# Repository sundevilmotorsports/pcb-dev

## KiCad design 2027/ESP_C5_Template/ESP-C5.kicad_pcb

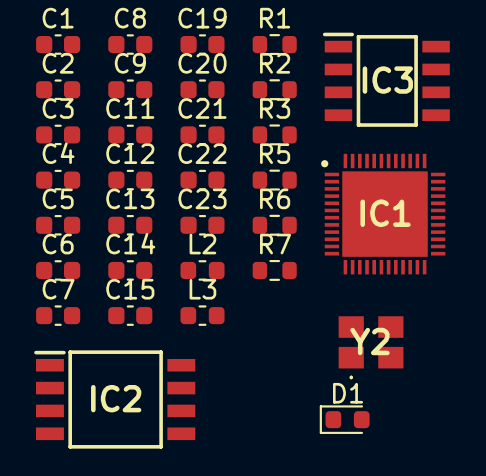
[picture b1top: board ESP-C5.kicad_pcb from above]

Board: 2 copper layers, 32 parts (0 on the bottom side), 20 nets, no tracks yet.

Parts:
C1: 0.8pF; C_0603_1608Metric
C2, C3: 12pF; C_0603_1608Metric
C4: 0.3pF; C_0603_1608Metric
C5, C19, C23: 10uF; C_0603_1608Metric
C6, C8, C14: 1uF; C_0603_1608Metric
C7, C11, C13, C20, C22: 0.1uF; C_0603_1608Metric
C9: 2.6pF; C_0603_1608Metric
C12: 10nF; C_0603_1608Metric
C15: 1 uF; C_0603_1608Metric
C21: 3.0pF; C_0603_1608Metric
D1: D_TVS (ESD); D_0603_1608Metric
IC1: ESP32-C5HR8; QFN40P600X600X90-49N-D
IC2: SST26VF064B-104I_SM; SOIC127P794X203-8N
IC3: IS66WVR8M8FBLL-104NLI; SOIC127P600X175-8N
L2: 24nH; L_0603_1608Metric
L3: 2nH; L_0603_1608Metric
R1: 499; R_0603_1608Metric
R2, R3, R5, R6, R7: 0; R_0603_1608Metric
Y2: CX3225FB48000F0FZZH1

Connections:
/SPICLK: IC2.6 (CLK), IC3.6 (CLK), R6.2
/SPICS0: IC1.26 (SPICS0), IC2.1 (~CS)
/SPICS1_IO15: IC1.25 (SPICS1), IC3.1 (~CS)
/SPID: IC2.5 (DI), IC3.5 (DI), R7.2
/SPIHD: IC2.7 (~HOLD), IC3.7 (~HOLD), R5.2
/SPIQ: IC2.2 (DO), IC3.2 (DO), R2.2
/SPIWP: IC2.3 (~WP), IC3.3 (~WP), R3.2
/VDD33: C1.1, C4.1, C5.1, C6.1, C7.1, C8.1, C11.1, C12.1, C13.1, C14.1, C19.1, C21.1, C22.1, C23.1, D1.1 (A1), IC1.1 (VDDA6), IC1.3 (VDDA7), IC1.6 (VDDA8), IC1.8 (VDDPST1), IC1.24 (VDDPST2), IC1.39 (VDDPST3), IC1.44 (VDDA3), IC1.45 (VDDA4), IC1.46 (VDDA5), L3.2
/VDD_SPI: C15.1, C20.1, IC1.29 (VDD_SPI), IC2.8 (VDD), IC3.8 (VDD)
/XTAL_N: C2.2, IC1.4 (XTAL_N), Y2.3 (X_OUT)
/XTAL_P: C3.2, L2.1, Y2.1 (X_IN)
GND: C1.2, C2.1, C3.1, C4.2, C5.2, C6.2, C7.2, C8.2, C9.2, C11.2, C12.2, C13.2, C14.2, C15.2, C19.2, C20.2, C21.2, C22.2, C23.2, D1.2 (A2), IC1.2 (GND_1), IC1.43 (GND_2), IC1.47 (GND_3), IC1.49 (GND_4), IC2.4 (GND), IC3.4 (GND), Y2.2 (GND_1), Y2.4 (GND_2)
unnamed: IC1.31 (SPICLK), R6.1
unnamed: IC1.32 (SPID), R7.1
unnamed: IC1.30 (SPIHD), R5.1
unnamed: IC1.27 (SPIQ), R2.1
unnamed: IC1.28 (SPIWP), R3.1
unnamed: IC1.20 (U0TXD), R1.1
unnamed: C9.1, IC1.40 (VDDA1), IC1.41 (VDDA2), L3.1
unnamed: IC1.5 (XTAL_P), L2.2

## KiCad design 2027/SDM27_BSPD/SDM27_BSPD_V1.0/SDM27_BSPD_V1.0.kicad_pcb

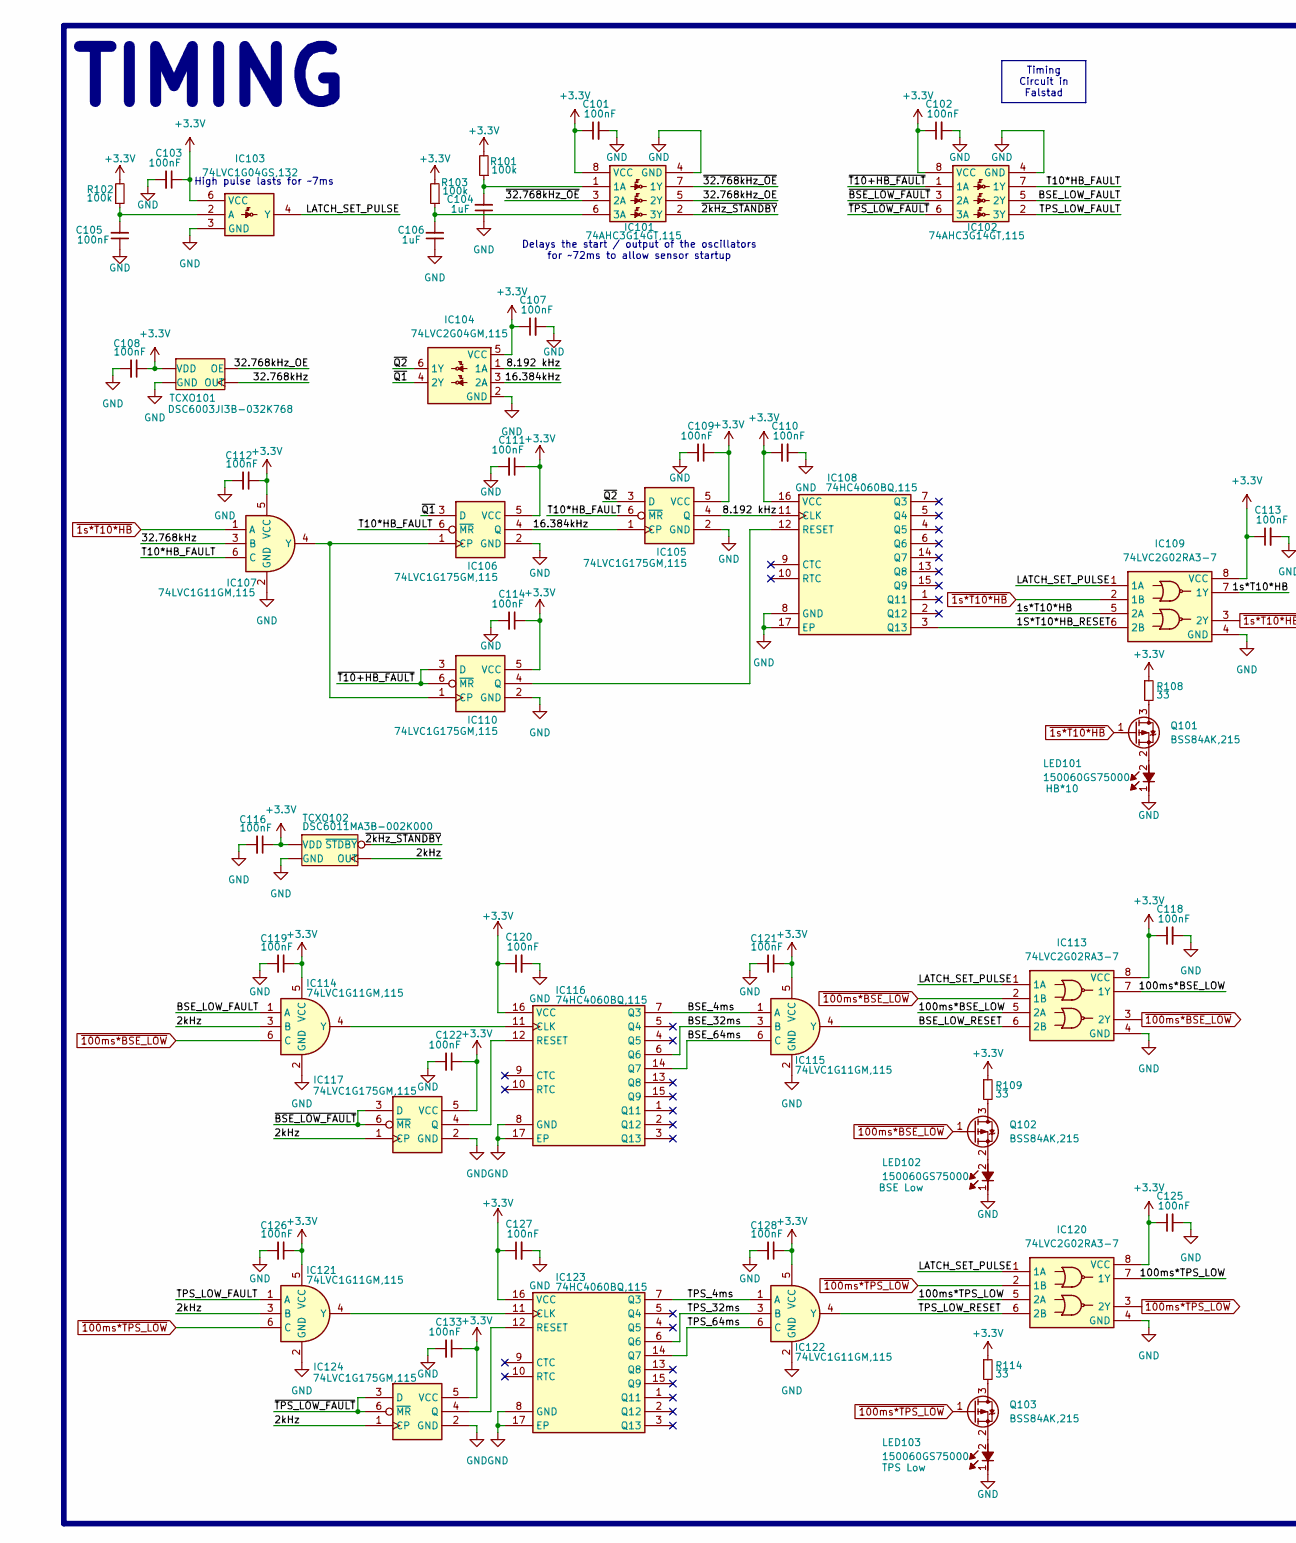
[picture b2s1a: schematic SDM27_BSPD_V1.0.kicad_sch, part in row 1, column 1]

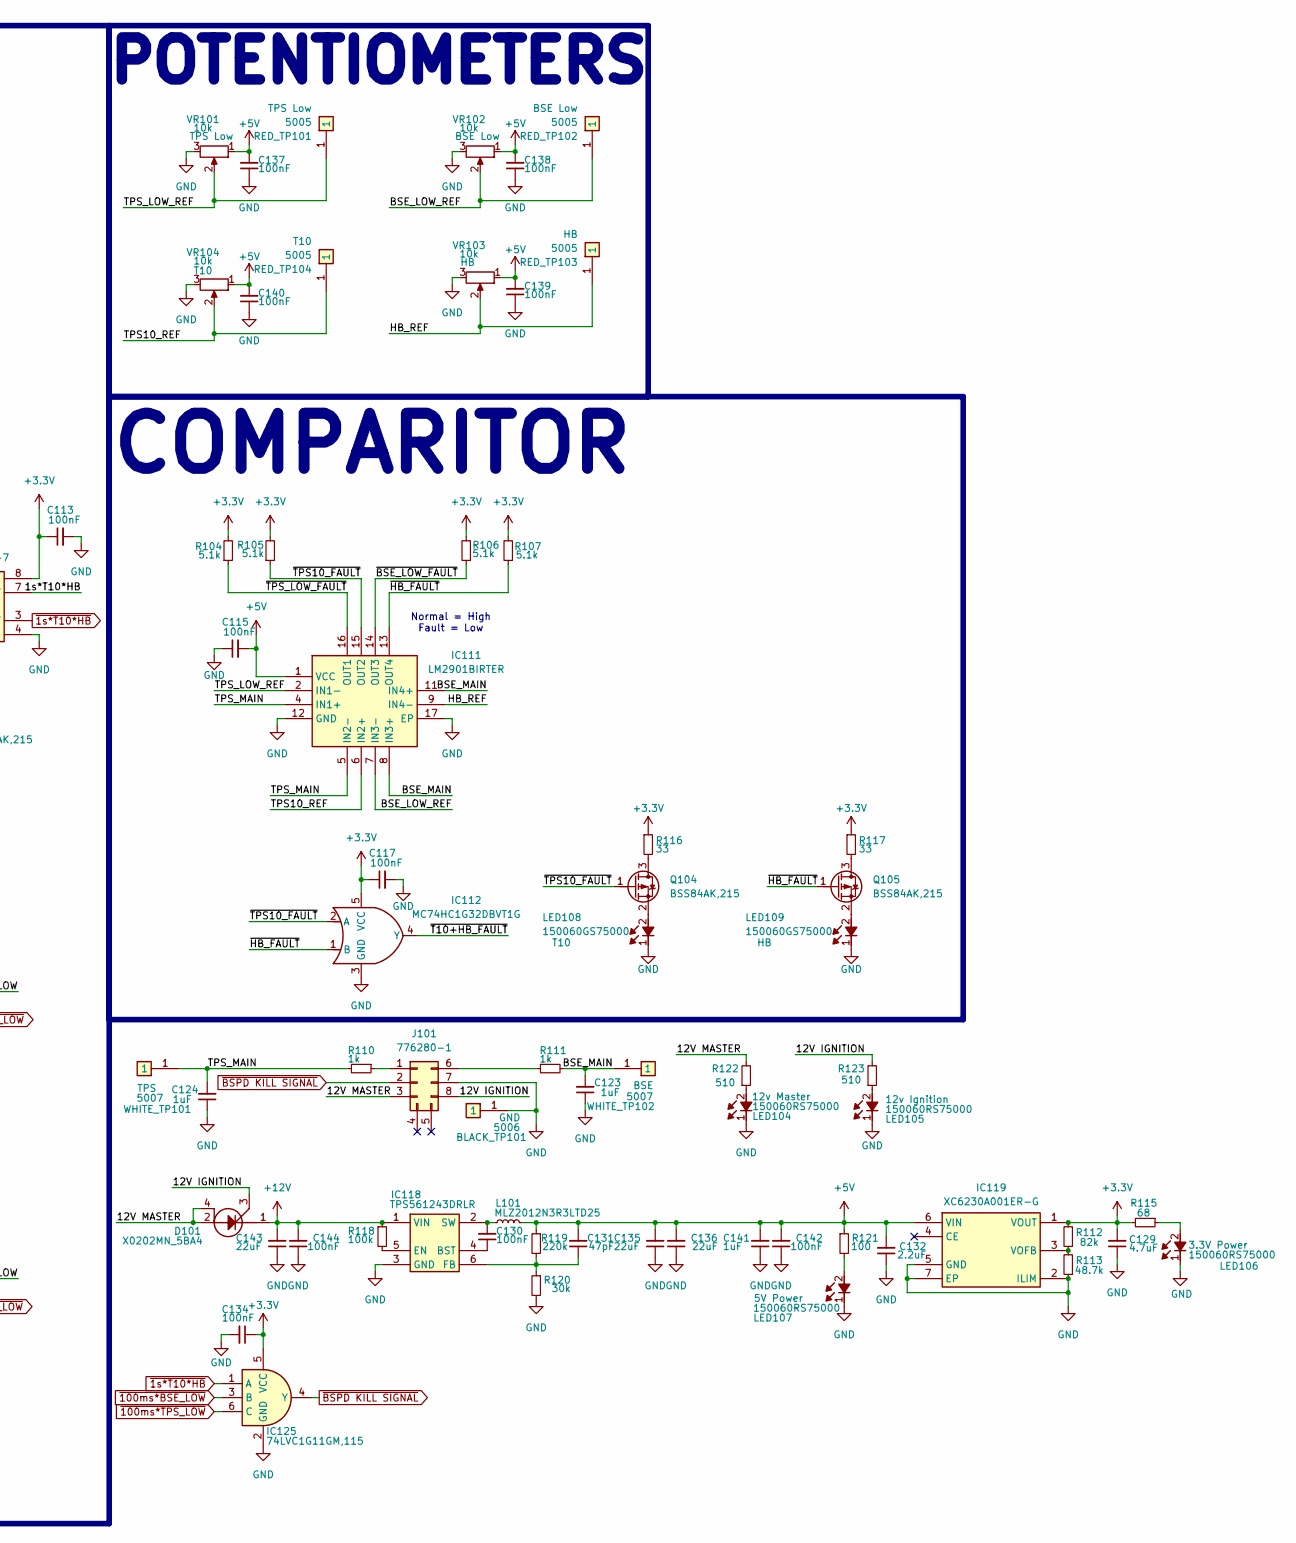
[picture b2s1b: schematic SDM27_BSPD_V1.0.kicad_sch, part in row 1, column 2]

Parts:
BLACK_TP101: 5006; Mouser Part Number 534-5006
C101, C102, C103, C105, C107, C108, C109, C110, C111, C112, C113, C114, C115, C116, C117, C118, C119, C120, C121, C122, C125, C126, C127, C128, C130, C133, C134, C137, C138, C139, C140, C142, C144: 100nF; C_0603_1608Metric
C104, C106, C123, C124, C141: 1uF; C_0603_1608Metric
C129: 4.7uF; C_0603_1608Metric
C131: 47pF; C_0603_1608Metric
C132: 2.2uF; C_0603_1608Metric
C135, C136: 22uF; C_0805_2012Metric
C143: 22uF; C_0603_1608Metric
D101: X0202MN_5BA4; SOT230P700X190-4N; Mouser Part Number 511-X0202MN
IC101, IC102: 74AHC3G14GT,115; 74AVC9112GTX; Mouser Part Number 771-74AHC3G14GT115
IC103: 74LVC1G04GS,132; 74LVC1G3157GS132; Mouser Part Number 771-74LVC1G04GS132
IC104: 74LVC2G04GM,115; PESD3V3L5UF115; Mouser Part Number 771-LVC2G04GM115
IC105, IC106, IC110, IC117, IC124: 74LVC1G175GM,115; PESD3V3L5UF115; Mouser Part Number 771-LVC1G175GM115
IC107, IC114, IC115, IC121, IC122, IC125: 74LVC1G11GM,115; PESD3V3L5UF115; Mouser Part Number 771-LVC1G11GM115
IC108, IC116, IC123: 74HC4060BQ,115; 74HC4060BQ115; Mouser Part Number 771-74HC4060BQ,115
IC109, IC113, IC120: 74LVC2G02RA3-7; 74LVC2G02RA37; Mouser Part Number 621-74LVC2G02RA3-7
IC111: LM2901BIRTER; QFN50P300X300X80-17N-D; Mouser Part Number 595-LM2901BIRTER
IC112: MC74HC1G32DBVT1G; SOT95P275X110-5L; Mouser Part Number 863-MC74HC1G32DBVT1G
IC118: TPS561243DRLR; SOTFL50P160X60-6L; Mouser Part Number 595-TPS561243DRLR
IC119: XC6230A001ER-G; XD9264D75DERQ; Manufacturer_Part_Number XC6230A001ER-G
J101: 776280-1; Mouser Part Number 571-776280-1
L101: MLZ2012N3R3LTD25; INDC2012X105L; Mouser Part Number 810-MLZ2012N3R3LTD25
LED101, LED102, LED103, LED108, LED109: 150060GS75000; LEDC1608X80N; Mouser Part Number 710-150060GS75000
LED104, LED105, LED106, LED107: 150060RS75000; LEDC1608X80N; Mouser Part Number 710-150060RS75000
Q101, Q102, Q103, Q104, Q105: BSS84AK,215; SOT95P230X110-3L; Mouser Part Number 771-BSS84AK215
R101, R102, R103, R118: 100k; R_0603_1608Metric
R104, R105, R106, R107: 5.1k; R_0603_1608Metric
R108, R109, R114, R116, R117: 33; R_0603_1608Metric
R110, R111: 1k; R_0603_1608Metric
R112: 82k; R_0603_1608Metric
R113: 48.7k; R_0603_1608Metric
R115: 68; R_0603_1608Metric
R119: 220k; R_0603_1608Metric
R120: 30k; R_0603_1608Metric
R121: 100; R_0603_1608Metric
R122, R123: 510; R_0603_1608Metric
RED_TP101, RED_TP102, RED_TP103, RED_TP104: 5005; Mouser Part Number 534-5005
TCXO101: DSC6003JI3B-032K768; Mouser Part Number 579-D6003JI3B032K768
TCXO102: DSC6011MA3B-002K000; Mouser Part Number 579-C6011MA3B02K000
VR101, VR102, VR103, VR104: 10k; 3386P1103TLF; Mouser Part Number 652-3386P-1-103TLF
WHITE_TP101, WHITE_TP102: 5007; Mouser Part Number 534-5007

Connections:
+3.3V: C101.1, C102.1, C103.1, C107.1, C108.1, C109.1, C110.1, C111.1, C112.1, C113.1, C114.1, C116.1, C117.1, C118.1, C119.1, C120.1, C121.1, C122.1, C125.1, C126.1, C127.1, C128.1, C129.2, C133.1, C134.1, IC101.8 (VCC), IC102.8 (VCC), IC103.6 (VCC), IC104.5 (VCC), IC105.5 (VCC), IC106.5 (VCC), IC107.5 (VCC), IC108.16 (VCC), IC109.8 (VCC), IC110.5 (VCC), IC112.5 (VCC), IC113.8 (VCC), IC114.5 (VCC), IC115.5 (VCC), IC116.16 (VCC), IC117.5 (VCC), IC119.1 (VOUT), IC120.8 (VCC), IC121.5 (VCC), IC122.5 (VCC), IC123.16 (VCC), IC124.5 (VCC), IC125.5 (VCC), R101.2, R102.2, R103.2, R104.2, R105.2, R106.2, R107.2, R108.1, R109.1, R112.2, R114.1, R115.2, R116.1, R117.1, TCXO101.4 (VDD), TCXO102.4 (VDD)
+5V: C115.2, C131.2, C132.2, C135.2, C136.2, C137.2, C138.2, C139.2, C140.2, C141.2, C142.2, IC111.1 (VCC), IC119.6 (VIN), L101.2, R119.1, R121.1, VR101.1 (CCW), VR102.1 (CCW), VR103.1 (CCW), VR104.1 (CCW)
+12V: C143.2, C144.2, D101.1 (K), IC118.1 (VIN), R118.1
/1S*T10*HB_RESET: IC108.3 (Q13), IC109.6 (2B)
/1s*T10*HB: IC109.5 (2A), IC109.7 (1Y)
/2kHz: IC114.3 (B), IC117.1 (CP), IC121.3 (B), IC124.1 (CP), TCXO102.3 (OUT)
/8.192 kHz: IC104.1 (1A), IC105.4 (Q), IC108.11 (CLK)
/12V IGNITION: D101.3 (G), J101.8, R123.2
/12V MASTER: D101.2 (A_1), D101.4 (A_2), J101.3, R122.2
/16.384kHz: IC104.3 (2A), IC105.1 (CP), IC106.4 (Q)
/32.768kHz: IC107.3 (B), TCXO101.3 (OUT)
/32.768kHz_OE: IC101.5 (2Y), TCXO101.1 (OE)
/100ms*BSE_LOW: IC113.5 (2A), IC113.7 (1Y)
/100ms*TPS_LOW: IC120.5 (2A), IC120.7 (1Y)
/BSE_4ms: IC115.1 (A), IC116.7 (Q3)
/BSE_32ms: IC115.3 (B), IC116.6 (Q6)
/BSE_64ms: IC115.6 (C), IC116.14 (Q7)
/BSE_LOW_FAULT: IC102.5 (2Y), IC114.1 (A)
/BSE_LOW_REF: IC111.7 (IN3-), RED_TP102.1, VR102.2 (Wiper)
/BSE_LOW_RESET: IC113.6 (2B), IC115.4 (Y)
/BSE_MAIN: C123.2, IC111.8 (IN3+), IC111.11 (IN4+), R111.2, WHITE_TP102.1
/HB_REF: IC111.9 (IN4-), RED_TP103.1, VR103.2 (Wiper)
/LATCH_SET_PULSE: IC103.4 (Y), IC109.1 (1A), IC113.1 (1A), IC120.1 (1A)
/T10*HB_FAULT: IC102.7 (1Y), IC105.6 (~MR), IC106.6 (~MR), IC107.6 (C)
/TPS10_REF: IC111.6 (IN2+), RED_TP104.1, VR104.2 (Wiper)
/TPS_4ms: IC122.1 (A), IC123.7 (Q3)
/TPS_32ms: IC122.3 (B), IC123.6 (Q6)
/TPS_64ms: IC122.6 (C), IC123.14 (Q7)
/TPS_LOW_FAULT: IC102.2 (3Y), IC121.1 (A)
/TPS_LOW_REF: IC111.2 (IN1-), RED_TP101.1, VR101.2 (Wiper)
/TPS_LOW_RESET: IC120.6 (2B), IC122.4 (Y)
/TPS_MAIN: C124.2, IC111.4 (IN1+), IC111.5 (IN2-), R110.2, WHITE_TP101.1
/~2kHz_STANDBY: IC101.2 (3Y), TCXO102.1 (~STDBY)
/~32.768kHz_OE: IC101.3 (2A), IC101.7 (1Y)
/~BSE_LOW_FAULT: IC102.3 (2A), IC111.14 (OUT3), IC117.3 (D), IC117.6 (~MR), R106.1
/~HB_FAULT: IC111.13 (OUT4), IC112.1 (B), Q105.1 (G), R107.1
/~Q1: IC104.4 (2Y), IC106.3 (D)
/~Q2: IC104.6 (1Y), IC105.3 (D)
/~T10+HB_FAULT: IC102.1 (1A), IC110.3 (D), IC110.6 (~MR), IC112.4 (Y)
/~TPS10_FAULT: IC111.15 (OUT2), IC112.2 (A), Q104.1 (G), R105.1
/~TPS_LOW_FAULT: IC102.6 (3A), IC111.16 (OUT1), IC124.3 (D), IC124.6 (~MR), R104.1
GND: BLACK_TP101.1, C101.2, C102.2, C103.2, C104.1, C105.1, C106.1, C107.2, C108.2, C109.2, C110.2, C111.2, C112.2, C113.2, C114.2, C115.1, C116.2, C117.2, C118.2, C119.2, C120.2, C121.2, C122.2, C123.1, C124.1, C125.2, C126.2, C127.2, C128.2, C129.1, C132.1, C133.2, C134.2, C135.1, C136.1, C137.1, C138.1, C139.1, C140.1, C141.1, C142.1, C143.1, C144.1, IC101.4 (GND), IC102.4 (GND), IC103.3 (GND), IC104.2 (GND), IC105.2 (GND), IC106.2 (GND), IC107.2 (GND), IC108.8 (GND), IC108.17 (EP), IC109.4 (GND), IC110.2 (GND), IC111.12 (GND), IC111.17 (EP), IC112.3 (GND), IC113.4 (GND), IC114.2 (GND), IC115.2 (GND), IC116.8 (GND), IC116.17 (EP), IC117.2 (GND), IC118.3 (GND), IC119.2 (ILIM), IC119.5 (GND), IC119.7 (EP), IC120.4 (GND), IC121.2 (GND), IC122.2 (GND), IC123.8 (GND), IC123.17 (EP), IC124.2 (GND), IC125.2 (GND), J101.7, LED101.1 (K), LED102.1 (K), LED103.1 (K), LED104.1 (K), LED105.1 (K), LED106.1 (K), LED107.1 (K), LED108.1 (K), LED109.1 (K), R113.1, R120.2, TCXO101.2 (GND), TCXO102.2 (GND), VR101.3 (CW), VR102.3 (CW), VR103.3 (CW), VR104.3 (CW)
unnamed: C104.2, IC101.1 (1A), R101.1
unnamed: C106.2, IC101.6 (3A), R103.1
unnamed: C105.2, IC103.2 (A), R102.1
unnamed: IC106.1 (CP), IC107.4 (Y), IC110.1 (CP)
unnamed: IC108.12 (RESET), IC110.4 (Q)
unnamed: IC114.4 (Y), IC116.11 (CLK)
unnamed: IC116.12 (RESET), IC117.4 (Q)
unnamed: C130.1, IC118.4 (BST)
unnamed: IC118.5 (EN), R118.2
unnamed: C131.1, IC118.6 (FB), R119.2, R120.1
unnamed: C130.2, IC118.2 (SW), L101.1
unnamed: IC119.3 (VOFB), R112.1, R113.2
unnamed: IC121.4 (Y), IC123.11 (CLK)
unnamed: IC123.12 (RESET), IC124.4 (Q)
unnamed: J101.1, R110.1
unnamed: J101.6, R111.1
unnamed: LED101.2 (A), Q101.2 (S)
unnamed: LED102.2 (A), Q102.2 (S)
unnamed: LED103.2 (A), Q103.2 (S)
unnamed: LED104.2 (A), R122.1
unnamed: LED105.2 (A), R123.1
unnamed: LED106.2 (A), R115.1
unnamed: LED107.2 (A), R121.2
unnamed: LED108.2 (A), Q104.2 (S)
unnamed: LED109.2 (A), Q105.2 (S)
unnamed: Q101.3 (D), R108.2
unnamed: Q102.3 (D), R109.2
unnamed: Q103.3 (D), R114.2
unnamed: Q104.3 (D), R116.2
unnamed: Q105.3 (D), R117.2
~1s*T10*HB: IC107.1 (A), IC109.2 (1B), IC109.3 (2Y), IC125.1 (A), Q101.1 (G)
~100ms*BSE_LOW: IC113.2 (1B), IC113.3 (2Y), IC114.6 (C), IC125.3 (B), Q102.1 (G)
~100ms*TPS_LOW: IC120.2 (1B), IC120.3 (2Y), IC121.6 (C), IC125.6 (C), Q103.1 (G)
~BSPD KILL SIGNAL: IC125.4 (Y), J101.2

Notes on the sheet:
POTENTIOMETERS
High pulse lasts for ~7ms
Delays the start / output of the oscillators for ~72ms to allow sensor startup
COMPARITOR
TIMING
Normal = High Fault = Low
Timing Circuit in Falstad

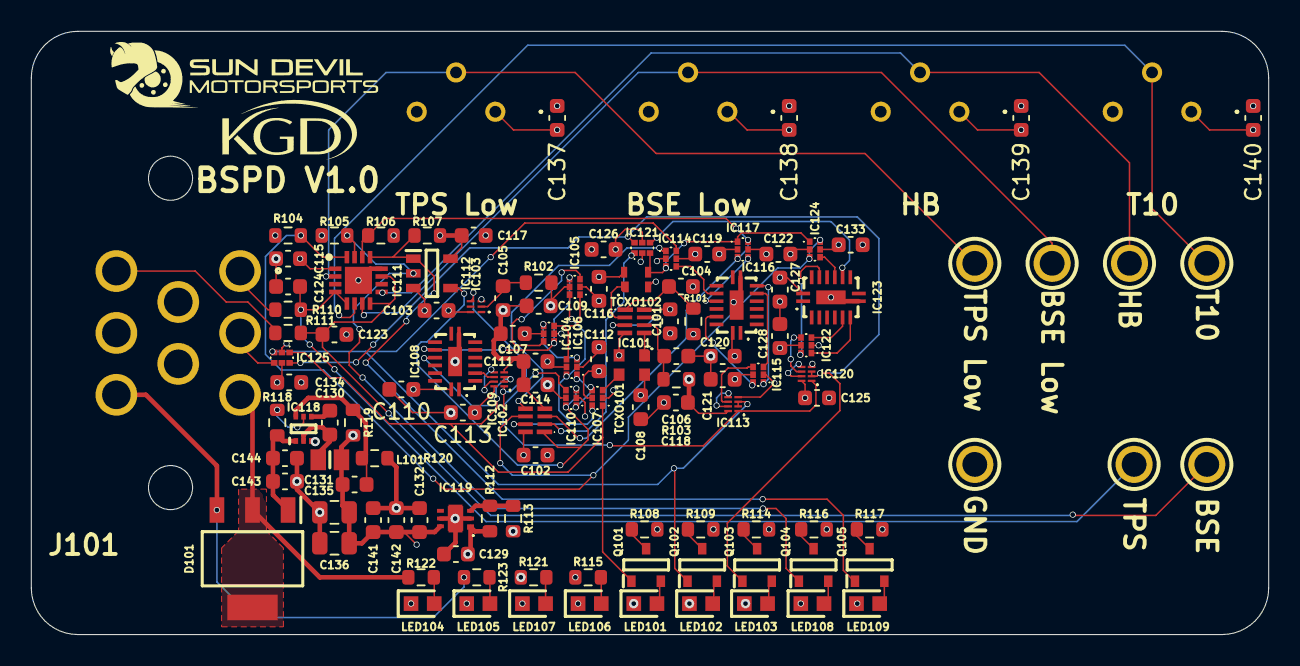
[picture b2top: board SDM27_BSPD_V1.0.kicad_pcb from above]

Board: 4 copper layers, 80.0 x 39.0 mm, 122 parts (0 on the bottom side), 76 nets.

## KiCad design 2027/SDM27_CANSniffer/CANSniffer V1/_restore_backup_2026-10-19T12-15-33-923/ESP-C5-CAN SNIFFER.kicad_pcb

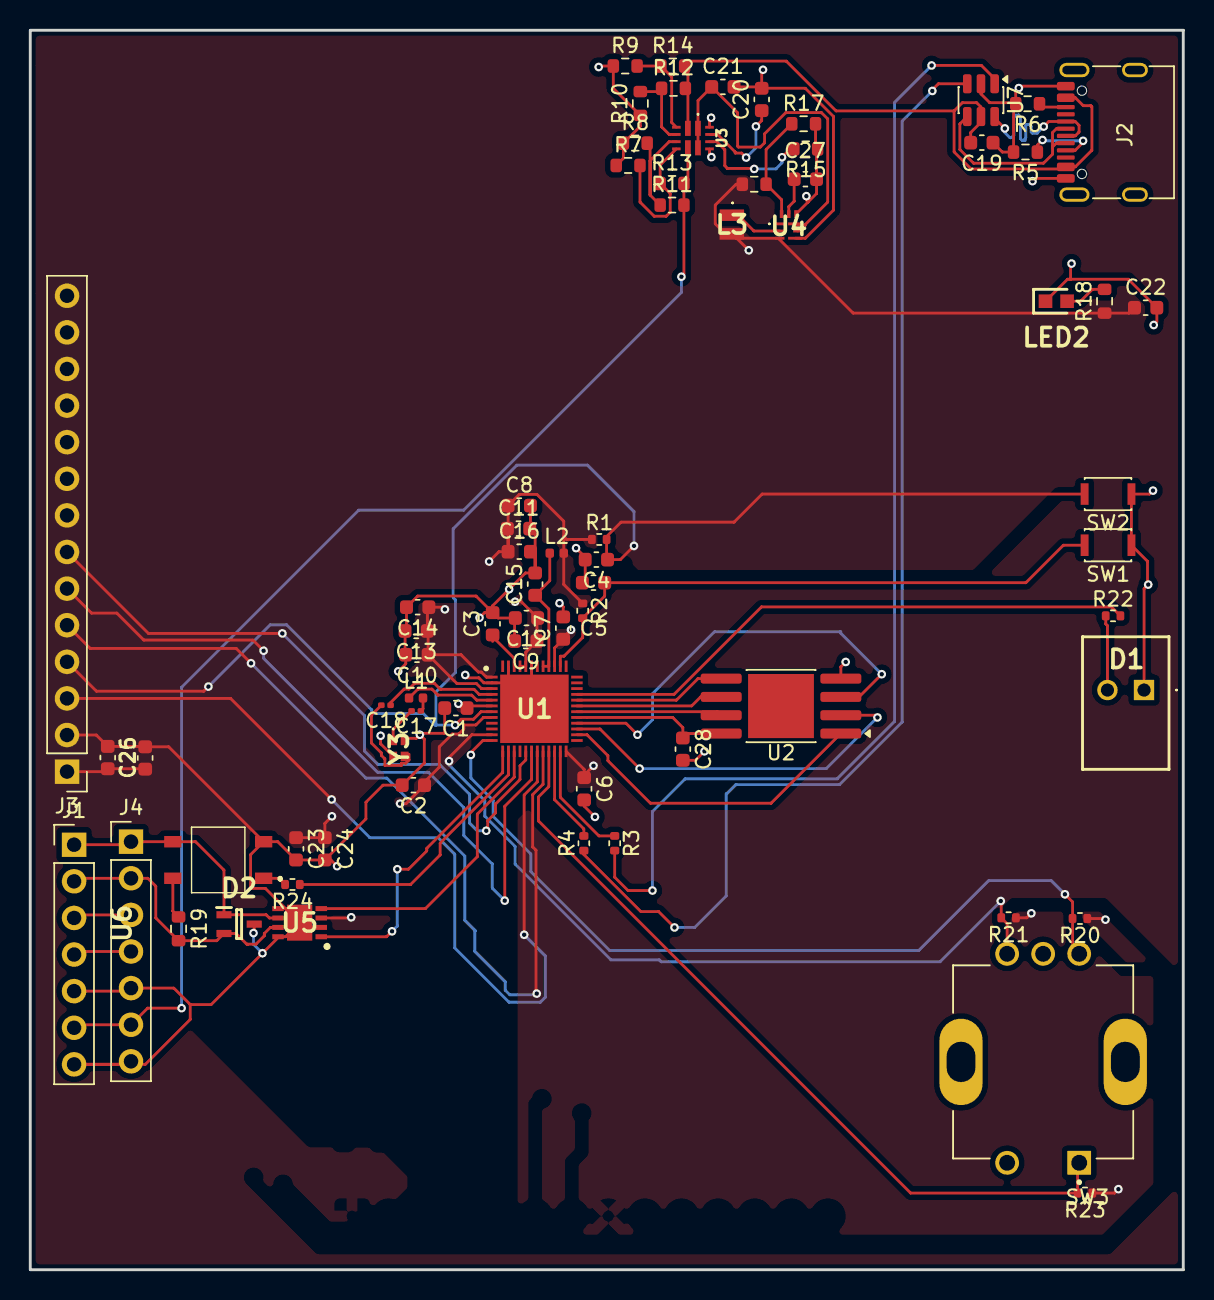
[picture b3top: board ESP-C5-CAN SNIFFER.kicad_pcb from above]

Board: 4 copper layers, 80.0 x 86.0 mm, 73 parts (0 on the bottom side), 57 nets.

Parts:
C1, C2, C3, C4, C5: 1uF; C_0603_1608Metric
C6, C7, C8, C9, C19, C23, C24, C25, C28: 100nF; C_0603_1608Metric
C10, C11, C12, C26: 10uF; C_0603_1608Metric
C13: 0.3pF; C_0603_1608Metric
C14: 0.8pF; C_0603_1608Metric
C15: 2.6pF; C_0603_1608Metric
C16: 3pF; C_0603_1608Metric
C17, C18: 12pF; C_0201_0603Metric
C20: 1uF 10V 0603; C_0603_1608Metric
C21: 10uF 25V; C_0603_1608Metric
C22: 22uF; C_0603_1608Metric
C27: 10nF; C_0603_1608Metric
D1: LED; SSFLXH100LID01
D2: ESDCAN03-2BWY; SOT65P210X110-3N
J1, J4: WEIPU SA12 7PIN; PinHeader_1x07_P2.54mm_Vertical
J2: USB_C_Receptacle_USB2.0_16P; USB_C_Receptacle_G-Switch_GT-USB-7010ASVCAN
J3: ELECROW_2.8_ILI9341; PinHeader_1x14_P2.54mm_Vertical
L1: 24nH; L_0402_1005Metric
L2: 2.0nH; L_0402_1005Metric
L3: F1C1-201612-2R2M; F1C12016122R2M
LED2: 150060RS75000; LEDC1608X80N
R1, R2, R20, R21, R23: 10k; R_0402_1005Metric
R3, R4: 27; R_0402_1005Metric
R5, R6: 5.1k; R_0603_1608Metric
R7, R8, R9, R10: 5k; R_0603_1608Metric
R11: 63.4k; R_0603_1608Metric
R12: 23.7k; R_0603_1608Metric
R13: 18.2k; R_0603_1608Metric
R14: 10.2k; R_0603_1608Metric
R15: 100k; R_0603_1608Metric
R16: 113k; R_0603_1608Metric
R17: 24.9k; R_0603_1608Metric
R18: 330; R_0603_1608Metric
R19: 100; R_0603_1608Metric
R22, R24: 1k; R_0402_1005Metric
SW1, SW2: SW_Push; SW_SPST_CK_KXT3
SW3: RotaryEncoder_Bourns_PEC11R-Switch_Vertical; XDCR_PEC11R-4220F-S0024
U1: ESP32-C5HR8; QFN40P600X600X90-49N-D
U2: GD25Q32ESIG; SOP-8-1EP_4.57x4.57mm_P1.27mm_EP4.57x4.45mm
U3: TPS2121RUXR
U4: TPS62901RPJR
U5: TCAN3403DRBRQ1; SON65P300X300X100-9N-D
U6: TLP175A_TPL,E; TLP266J
U7: USBLC6-2SC6; SOT-23-6
Y3: CX1612DB48000D0FPJC1

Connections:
+3.3V: C1.1, C2.1, C6.1, C7.1, C8.1, C9.1, C10.1, C11.1, C12.1, C13.1, C14.1, C16.1, C22.1, C23.1, C24.1, C25.2, C26.1, J3.1, J3.8, L2.2, L3.2, R1.1, R2.1, R16.1, R18.1, R20.1, R21.1, R23.1, U1.1 (VDDA6), U1.3 (VDDA7), U1.6 (VDDA8), U1.8 (VDDPST1), U1.24 (VDDPST2), U1.39 (VDDPST3), U1.44 (VDDA3), U1.45 (VDDA4), U4.3 (VOS), U5.3 (VCC)
+12V: J1.6, J4.6, R11.2, R13.2, U3.7 (IN1)
/BOOT: C5.1, R2.2, SW1.2, U1.38 (BOOT)
/CAN+: D2.2, J1.2, J4.2, R19.2, U5.7 (CANH)
/CAN+OUT: J1.4, J4.4
/CAN-: D2.1, J1.1, J4.1, U5.6 (CANL), U6.4
/CAN-OUT: J1.3, J4.3
/CAN_ACTIVITY_LED: R22.2, U1.33 (GPIO23)
/CAN_CTX: U1.13 (GPIO4), U5.1 (TXD)
/CAN_RTX: U1.15 (GPIO6), U5.4 (RXD)
/CAN_TERM: R24.1, U1.14 (GPIO5)
/CP: C4.1, J3.4, R1.2, SW2.2, U1.7 (CHIP_PU)
/ENC_A: R20.2, SW3.A, U1.12 (GPIO3)
/ENC_B: R21.2, SW3.B, U1.11 (GPIO2)
/ENC_SW: R23.2, SW3.S1, U1.21 (GPIO12)
/PWR_LED: LED2.2 (A), R18.2
/SPICLK: U1.31 (SPICLK), U2.6 (CLK)
/SPICS0: U1.26 (SPICS0), U2.1 (~CS)
/SPID: U1.32 (SPID), U2.5 (DI)
/SPIHD: U1.30 (SPIHD), U2.7 (~HOLD)
/SPIQ: U1.27 (SPIQ), U2.2 (DO)
/SPIWP: U1.28 (SPIWP), U2.3 (~WP)
/TFT_CS: J3.3, U1.19 (GPIO10)
/TFT_DC: J3.5, U1.20 (GPIO11)
/TFT_MOSI: J3.6, U1.18 (GPIO9)
/TFT_SCK: J3.7, U1.17 (GPIO8)
/USBM_D+: J2.A6 (D+), J2.B6 (D+), U7.6 (I/O1)
/USBM_D-: J2.A7 (D-), J2.B7 (D-), U7.4 (I/O2)
/USB_D+: R3.2, U7.1 (I/O1)
/USB_D-: R4.1, U7.3 (I/O2)
/VDD_SPI: C28.1, U1.29 (VDD_SPI), U2.8 (VDD)
GND: C1.2, C2.2, C3.2, C4.2, C5.2, C6.2, C7.2, C8.2, C9.2, C10.2, C11.2, C12.2, C13.2, C14.2, C15.2, C16.2, C19.1, C20.2, C21.2, C22.2, C23.2, C24.2, C25.1, C26.2, C27.2, C28.2, D1.1 (K), D2.3, J1.5, J1.7, J2.A1 (GND), J2.A12 (GND), J2.B1 (GND), J2.B12 (GND), J3.2, J4.5, J4.7, LED2.1 (K), R5.2, R6.2, R7.1, R8.1, R9.1, R10.1, R15.1, R17.2, SW1.1, SW2.1, SW3.C, SW3.MP, SW3.S2, U1.2 (GND_1), U1.43 (GND_2), U1.47 (GND_3), U1.49 (GND_4), U2.4 (GND), U3.9 (ST), U3.12 (GND), U4.4 (GND), U4.7 (CONFIG), U5.2 (GND), U5.5 (VIO), U5.8 (STB), U5.9 (EP), U6.3, U7.2 (GND), Y3.2, Y3.4
unnamed: C17.1, L1.2
unnamed: C17.2, Y3.1
unnamed: C18.2, Y3.3
unnamed: D1.2 (A), R22.1
unnamed: J2.A5 (CC1), R5.1
unnamed: J2.B5 (CC2), R6.1
unnamed: R19.1, U6.6
unnamed: R24.2, U6.1
unnamed: R4.2, U1.22 (GPIO13)
unnamed: R3.1, U1.23 (GPIO14)
unnamed: C15.1, L2.1, U1.40 (VDDA1), U1.41 (VDDA2)
unnamed: C3.1, U1.46 (VDDA5)
unnamed: C18.1, U1.4 (XTAL_N)
unnamed: L1.1, U1.5 (XTAL_P)
unnamed: R9.2, R14.1, U3.3 (CP2)
unnamed: R15.2, U3.10 (ILIM)
unnamed: R8.2, R11.1, U3.5 (OV1)
unnamed: R10.2, R12.1, U3.4 (OV2)
unnamed: R7.2, R13.1, U3.6 (PR1)
unnamed: C20.1, U3.11 (SS)
unnamed: C27.1, U4.8 (SS/TR)
unnamed: L3.1, U4.2 (SW)
unnamed: R16.2, R17.1, U4.9 (VSET)
VBUS: C19.2, J2.A4 (VBUS), J2.A9 (VBUS), J2.B4 (VBUS), J2.B9 (VBUS), R12.2, R14.2, U3.2 (IN2), U7.5 (VBUS)
VCC: C21.1, U3.1 (OUT_1), U3.8 (OUT_2), U4.5 (EN), U4.6 (VIN)

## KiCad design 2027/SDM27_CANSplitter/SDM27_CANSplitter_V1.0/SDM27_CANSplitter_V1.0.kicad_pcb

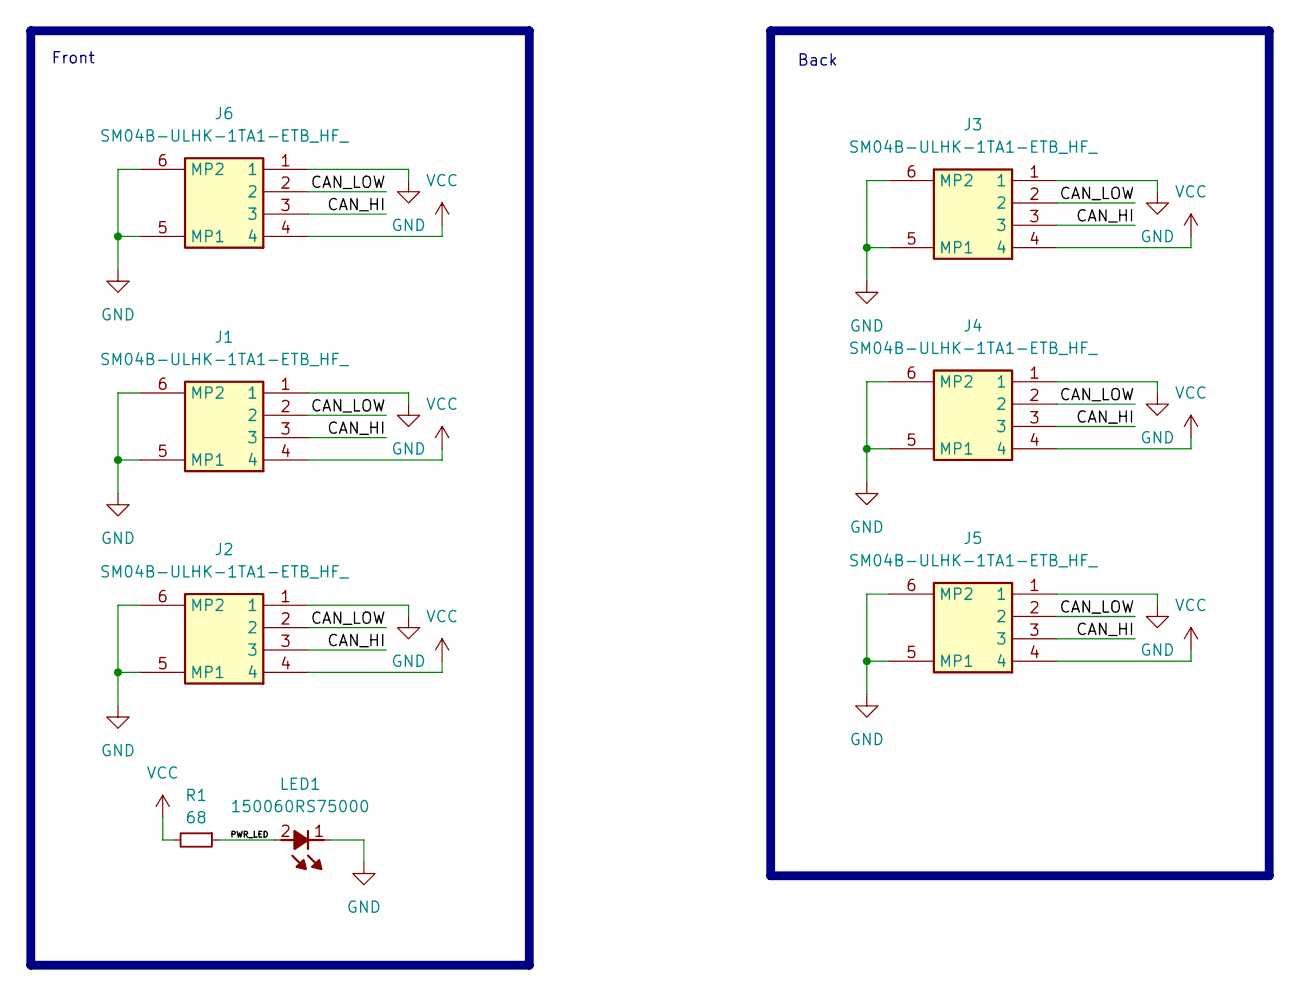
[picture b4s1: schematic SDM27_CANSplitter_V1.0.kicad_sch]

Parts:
J1, J2, J3, J4, J5, J6: SM04B-ULHK-1TA1-ETB_HF_; SM04BULHK1TA1ETBHF; Mouser Part Number 306-SM4BULH1TA1ETBHF
LED1: 150060RS75000; LEDC1608X80N; Mouser Part Number 710-150060RS75000
R1: 68; C_0603_1608Metric

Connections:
/CAN_HI: J1.3, J2.3, J3.3, J4.3, J5.3, J6.3
/CAN_LOW: J1.2, J2.2, J3.2, J4.2, J5.2, J6.2
/PWR_LED: LED1.2 (A), R1.1
GND: J1.1, J1.5 (MP1), J1.6 (MP2), J2.1, J2.5 (MP1), J2.6 (MP2), J3.1, J3.5 (MP1), J3.6 (MP2), J4.1, J4.5 (MP1), J4.6 (MP2), J5.1, J5.5 (MP1), J5.6 (MP2), J6.1, J6.5 (MP1), J6.6 (MP2), LED1.1 (K)
VCC: J1.4, J2.4, J3.4, J4.4, J5.4, J6.4, R1.2

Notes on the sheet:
Back
Front

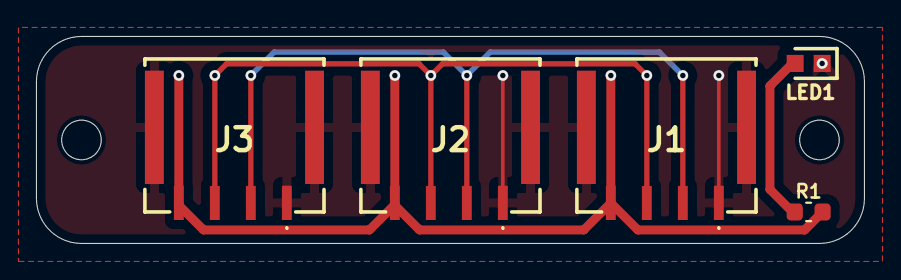
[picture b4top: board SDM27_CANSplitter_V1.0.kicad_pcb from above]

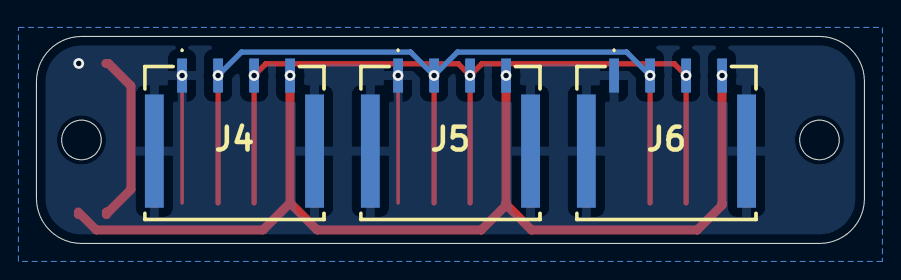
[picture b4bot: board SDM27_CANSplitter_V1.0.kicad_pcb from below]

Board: 2 copper layers, 46.0 x 11.5 mm, 8 parts (3 on the bottom side), 5 nets.

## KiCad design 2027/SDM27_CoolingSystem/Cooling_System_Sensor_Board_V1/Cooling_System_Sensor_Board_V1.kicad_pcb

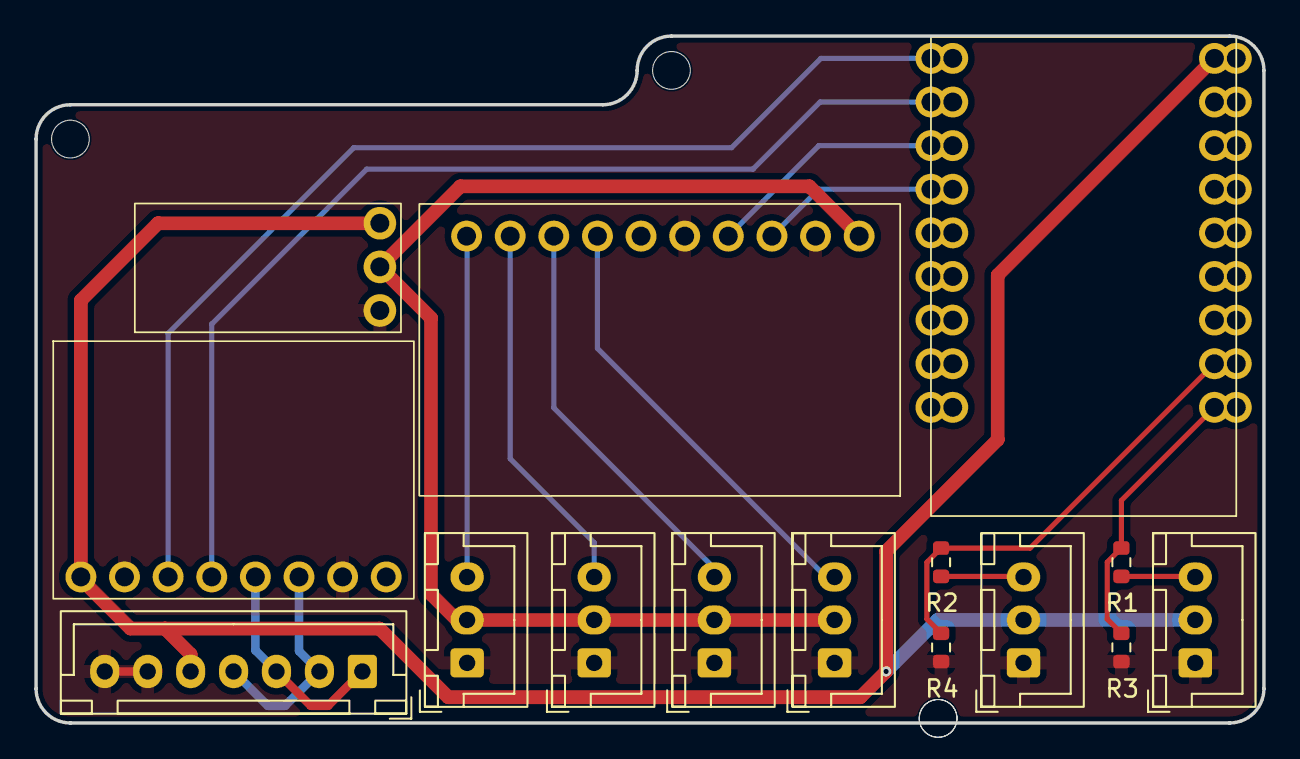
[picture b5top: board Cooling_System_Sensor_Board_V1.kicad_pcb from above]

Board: 2 copper layers, 71.5 x 40.0 mm, 15 parts (0 on the bottom side), 17 nets.

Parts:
J1: JST_XH_B7B-XH-A_1x07_P2.50mm_Vertical
J2: A1; JST_XH_B3B-XH-A_1x03_P2.50mm_Vertical
J3: A2; JST_XH_B3B-XH-A_1x03_P2.50mm_Vertical
J4: A3; JST_XH_B3B-XH-A_1x03_P2.50mm_Vertical
J5: A4; JST_XH_B3B-XH-A_1x03_P2.50mm_Vertical
J6: FLOW1; JST_XH_B3B-XH-A_1x03_P2.50mm_Vertical
J7: FLOW2; JST_XH_B3B-XH-A_1x03_P2.50mm_Vertical
M1: ESP32 C5 Mini
M2: TJA10423 CAD
M3: ADS1115ADC
M4: 3.3v LDO
R1, R2: 10K; R_0603_1608Metric
R3, R4: 20k; R_0603_1608Metric

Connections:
+3.3VA: J2.2, J3.2, J4.2, J5.2, M3.1 (VDD), M4.2 (3.3V)
+5V: J1.5, J6.2, J7.2, M1.9 (5V), M2.1 (VCC), M4.3 (VIN)
/Analog1: J2.3, M3.7 (A0)
/Analog2: J3.3, M3.8 (A1)
/Analog3: J4.3, M3.9 (A2)
/Analog4: J5.3, M3.10 (A3)
/CAN+: J1.1, J1.3, M2.5 (CANH)
/CAN-: J1.2, J1.4, M2.6 (CANL)
/CRX: M1.17 (IO6), M2.4 (CRX)
/CTX: M1.18 (IO5), M2.3 (CTX)
/FLOW1: J6.3, R2.1
/FLOW1lv: M1.2 (IO1), R2.2, R4.2
/FLOW2: J7.3, R1.1
/FLOW2lv: M1.1 (IO0), R1.2, R3.2
/SCL: M1.15 (IO8), M3.3 (SCL)
/SDA: M1.16 (IO7), M3.4 (SDA)
GND: J1.6, J1.7, J2.1, J3.1, J4.1, J5.1, J6.1, J7.1, M1.8 (GND), M2.2 (GND), M2.7 (S), M3.2 (GND), M3.5 (ADDR), M4.1 (GND), R3.1, R4.1
